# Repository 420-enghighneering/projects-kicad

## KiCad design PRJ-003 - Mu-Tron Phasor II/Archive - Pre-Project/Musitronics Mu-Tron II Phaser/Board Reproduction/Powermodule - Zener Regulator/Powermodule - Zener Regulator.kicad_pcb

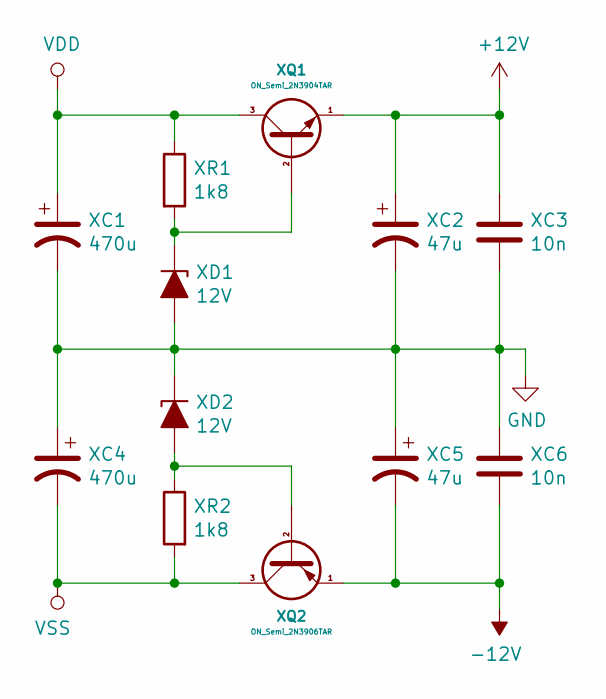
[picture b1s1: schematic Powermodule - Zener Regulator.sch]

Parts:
XC1, XC4: 470u; Electrolytic_Radial_Angled_D10.0_H17.0_P5.0
XC2, XC5: 47u; Electrolytic_Radial_Angled_D6.3_H11.0_P2.5
XC3, XC6: 10n; Wima_FKS2G021001C00KSSD
XD1, XD2: 12V; DO-41_P2.54
XQ1: ON_Semi_2N3904TAR
XQ2: ON_Semi_2N3906TAR
XR1, XR2: 1k8; R_CC25_P2.54_V

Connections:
+12V: XC2.1, XC3.1, XQ1.1 (E)
-12V: XC5.2, XC6.2, XQ2.1 (E)
GND: XC1.2, XC2.2, XC3.2, XC4.1, XC5.1, XC6.1, XD1.1 (A), XD2.2 (K)
unnamed: XD1.2 (K), XQ1.2 (B), XR1.2
unnamed: XD2.1 (A), XQ2.2 (B), XR2.1
VDD: XC1.1, XQ1.3 (C), XR1.1
VSS: XC4.2, XQ2.3 (C), XR2.2

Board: 2 copper layers, 12 parts (0 on the bottom side), 7 nets, no tracks yet.
